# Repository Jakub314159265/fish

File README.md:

## Bistable multivibrator that can be reset with light... and it is a **FISH**
## List of parts
- 3 * 2N3904 transistor
- 1 * GL5528 photoresistor
- 1 * 10k potentiometer
- 4 * 10k resistor
- 1 * 4k7 resitor
- 1 * 100 resitor
- 1 * 6mm push switch
- 1 * 5mm LED
- 1 * PinHeader_1x02_P2.54mm_Vertical
- 1 * battery holder

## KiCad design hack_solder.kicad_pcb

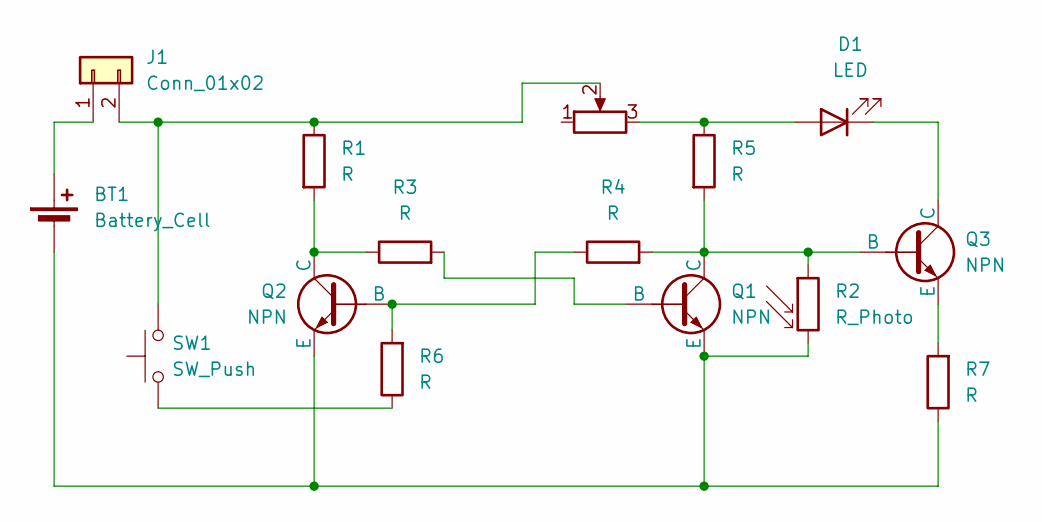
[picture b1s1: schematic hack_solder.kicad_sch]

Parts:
BT1: Battery_Cell; BatteryHolder_Keystone_3034_1x20mm
D1: LED; LED_D5.0mm
J1: Conn_01x02; PinHeader_1x02_P2.54mm_Vertical
Q1, Q2, Q3: NPN; TO-92L_HandSolder
R1, R3, R4, R5, R6, R7: R; R_Axial_DIN0207_L6.3mm_D2.5mm_P7.62mm_Horizontal
R2: R_Photo; R_LDR_5.1x4.3mm_P3.4mm_Vertical
RV1: P; Potentiometer_Vishay_T73YP_Vertical
SW1: SW_Push; SW_PUSH_6mm

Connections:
unnamed: BT1.1 (+), J1.1
unnamed: BT1.2 (-), Q1.3 (E), Q2.3 (E), R2.2, R7.1
unnamed: D1.2 (A), R5.1, RV1.3
unnamed: D1.1 (K), Q3.1 (C)
unnamed: J1.2, R1.1, RV1.2, SW1.2
unnamed: Q1.2 (B), R3.2
unnamed: Q1.1 (C), Q3.2 (B), R2.1, R4.2, R5.2
unnamed: Q2.2 (B), R4.1, R6.2
unnamed: Q2.1 (C), R1.2, R3.1
unnamed: Q3.3 (E), R7.2
unnamed: R6.1, SW1.1

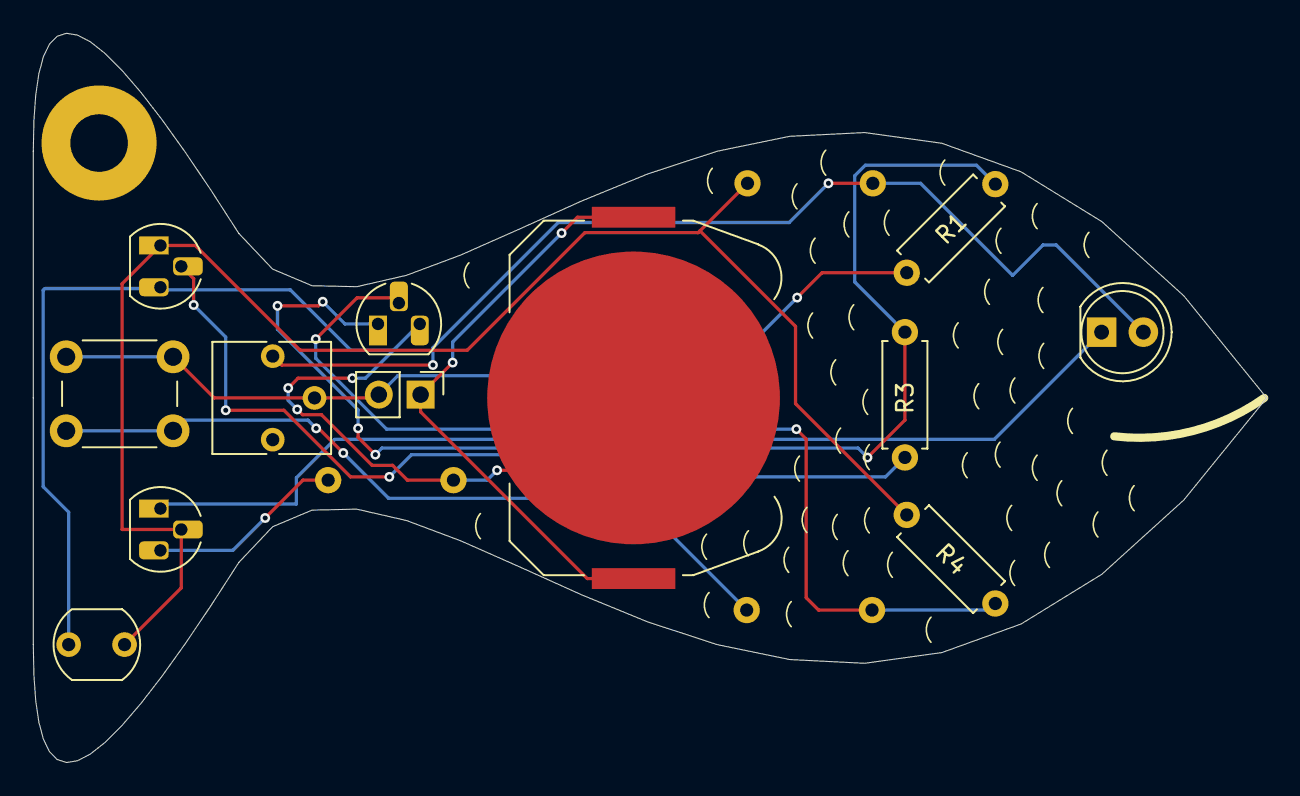
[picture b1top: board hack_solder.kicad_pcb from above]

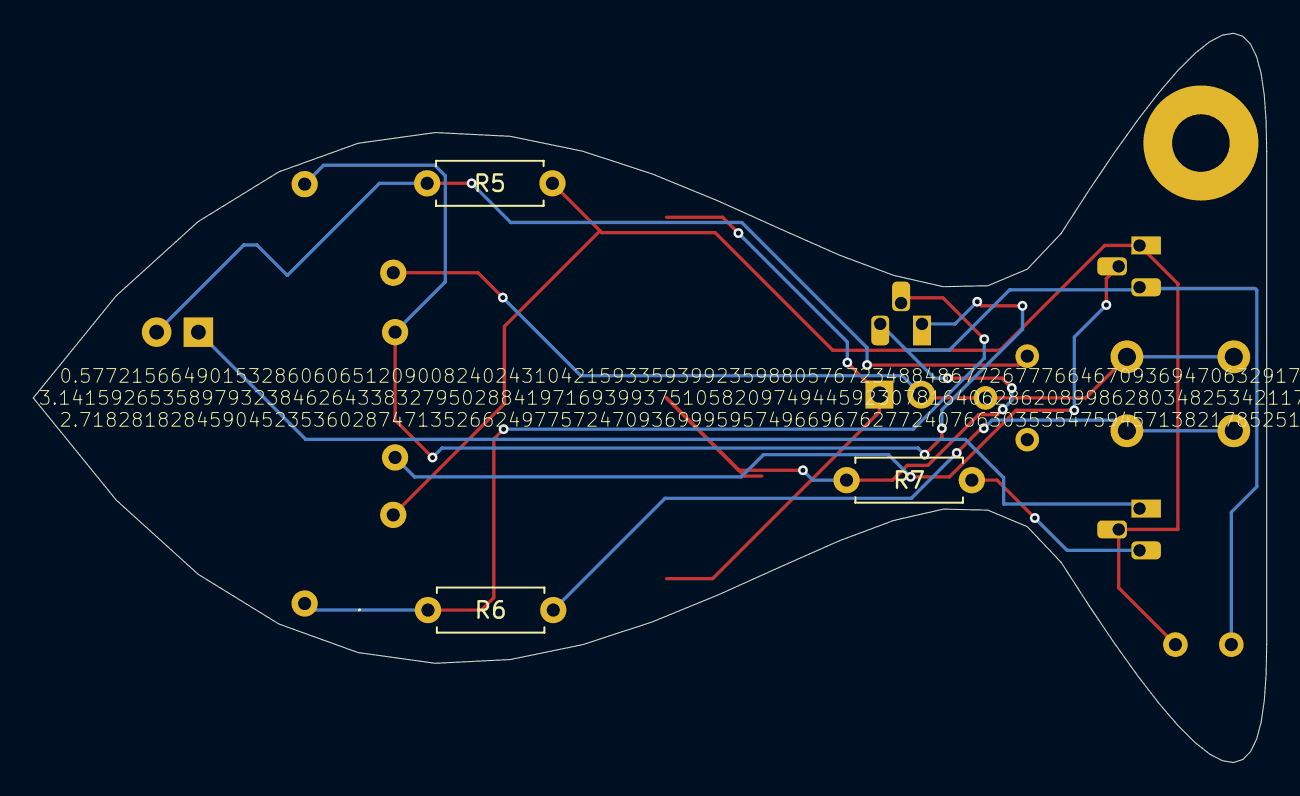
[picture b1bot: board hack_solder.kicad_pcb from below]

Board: 2 copper layers, 75.0 x 44.3 mm, 15 parts (3 on the bottom side), 11 nets.

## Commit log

2025-06-28 added pictures
2025-06-28 added files
2025-06-28 added kicad files
